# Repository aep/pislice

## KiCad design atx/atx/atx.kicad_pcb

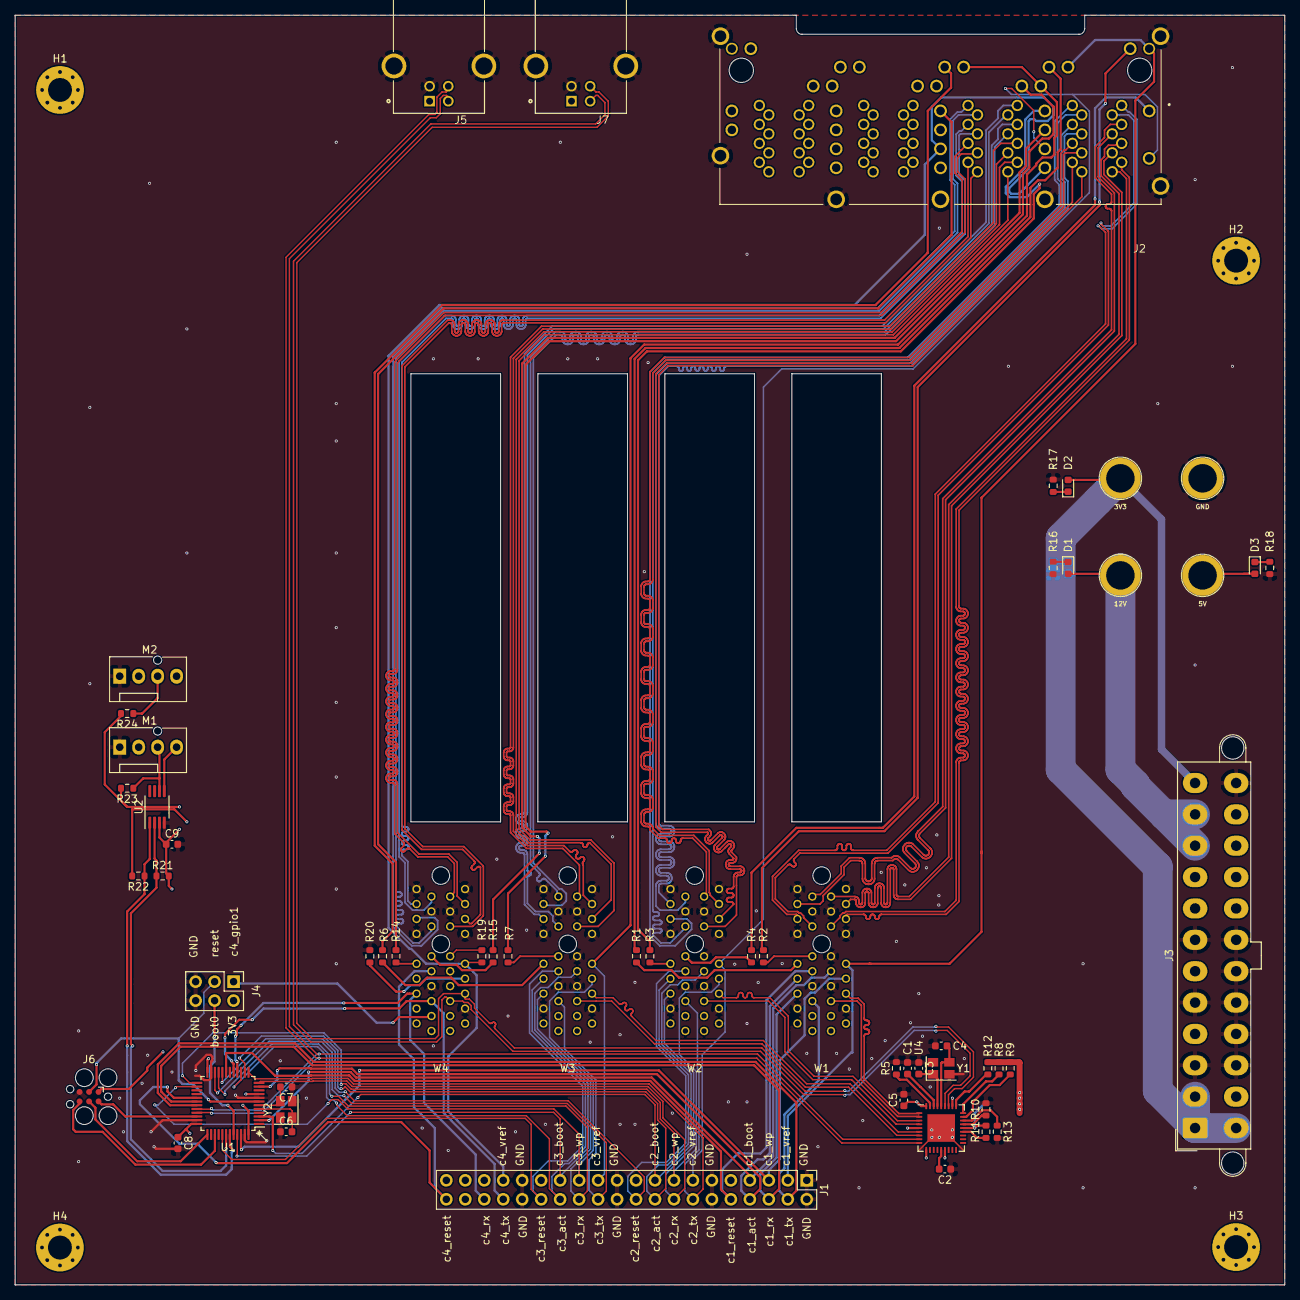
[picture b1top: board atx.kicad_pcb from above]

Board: 4 copper layers, 170.0 x 170.0 mm, 62 parts (0 on the bottom side), 116 nets.

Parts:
C1, C2: 0.1uF; C_0603_1608Metric
C3, C4, C6, C7: 14pF; C_0603_1608Metric
C5, C8: 10uF; C_0603_1608Metric
C9: 100nF; C_0603_1608Metric
D1, D2, D3: LED; LED_0603_1608Metric
H1, H2, H3, H4: MountingHole; MountingHole_3.2mm_M3_Pad_Via
J1: 2x20; PinHeader_2x20_P2.54mm_Vertical
J2: SS-74500-024; BEL_SS-74500-024
J3: ATX-24; Molex_Mini-Fit_Jr_5566-24A2_2x12_P4.20mm_Vertical
J4: Conn_02x03_Odd_Even; PinHeader_2x03_P2.54mm_Vertical
J5, J7: USB_B; CUI_UJ2-BH-1-TH
J6: Conn_02x03_Odd_Even; Tag-Connect_TC2030-IDC-FP_2x03_P1.27mm_Vertical
M1, M2: Fan_4pin; FanPinHeader_1x04_P2.54mm_Vertical
R1, R2, R3, R4, R6, R7, R14, R15, R17, R18: 300R; R_0603_1608Metric
R5: 12K 1%; R_0603_1608Metric
R8, R9, R10, R11, R12, R13: 10K; R_0603_1608Metric
R16, R19, R20: 1K; R_0603_1608Metric
R21, R22: 3K; R_0603_1608Metric
R23, R24: 36K 1%; R_0603_1608Metric
TP1: 12V; BANANA_CONN
TP2: 5V; BANANA_CONN
TP3: 3V3; BANANA_CONN
TP4: GND; BANANA_CONN
U1: STM32L151C8T6; LQFP-48_7x7mm_P0.5mm
U2: EMC2301; MSOP-8_3x3mm_P0.65mm
U4: USB2514B_Bi; QFN-36-1EP_6x6mm_P0.5mm_EP3.7x3.7mm
W1, W2, W3, W4: pislice-v1-PCIE-1X; piwing_pcie1
Y1, Y2: 24Mhz X1E0000210264; Crystal_SMD_SeikoEpson_TSX3225-4Pin_3.2x2.5mm

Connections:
+3V3: C5.1, C8.1, C9.1, D2.2, J3.1, J3.2, J3.12, J3.13, J4.2, J6.1, R8.2, R9.2, R11.2, R12.2, R21.2, R22.2, R23.2, R24.2, TP3.1, U1.9, U1.24, U1.36, U1.48, U2.3, U4.5, U4.10, U4.15, U4.23, U4.29, U4.36
+5V: D3.2, J3.4, J3.6, J3.21, J3.22, J3.23, TP2.1, W1.A1, W1.A2, W1.B1, W1.B2, W2.A1, W2.A2, W2.B1, W2.B2, W3.A1, W3.A2, W3.B1, W3.B2, W4.A1, W4.A2, W4.B1, W4.B2
+12V: D1.2, J3.10, J3.11, M1.2, M2.2, TP1.1
/c1_act: J1.8, U1.11, W1.A8
/c1_boot: J1.7, U1.2, W1.B9
/c1_eth_act: J2.12_1, R1.1
/c1_eth_link: J2.10_1, R2.1
/c1_eth_p1+: J2.8_1, W1.B13
/c1_eth_p1-: J2.7_1, W1.B14
/c1_eth_p2+: J2.6_1, W1.B16
/c1_eth_p2-: J2.5_1, W1.B17
/c1_eth_p3+: J2.4_1, W1.A16
/c1_eth_p3-: J2.3_1, W1.A17
/c1_eth_p4+: J2.2_1, W1.A13
/c1_eth_p4-: J2.1_1, W1.A14
/c1_reset: J1.10, U1.19, W1.A9
/c1_rx: J1.6, U1.30, W1.A6
/c1_tx: J1.4, U1.31, W1.A5
/c1_usb+: U4.2, W1.B5
/c1_usb-: U4.1, W1.B6
/c1_vref: J1.3, J2.9_1, J2.11_1, W1.B10
/c1_wp: J1.5, U1.46, W1.B8
/c2_act: J1.18, U1.14, W2.A8
/c2_boot: J1.17, U1.3, W2.B9
/c2_eth_act: J2.12_2, R3.1
/c2_eth_link: J2.10_2, R4.1
/c2_eth_p1+: J2.8_2, W2.B13
/c2_eth_p1-: J2.7_2, W2.B14
/c2_eth_p2+: J2.6_2, W2.B16
/c2_eth_p2-: J2.5_2, W2.B17
/c2_eth_p3+: J2.4_2, W2.A16
/c2_eth_p3-: J2.3_2, W2.A17
/c2_eth_p4+: J2.2_2, W2.A13
/c2_eth_p4-: J2.1_2, W2.A14
/c2_reset: J1.20, U1.20, W2.A9
/c2_rx: J1.16, U1.12, W2.A6
/c2_tx: J1.14, U1.13, W2.A5
/c2_usb+: U4.4, W2.B5
/c2_usb-: U4.3, W2.B6
/c2_vref: J1.13, J2.9_2, J2.11_2, W2.B10
/c2_wp: J1.15, U1.25, W2.B8
/c3_act: J1.28, U1.15, W3.A8
/c3_boot: J1.27, U1.45, W3.B9
/c3_eth_act: J2.12_3, R6.1
/c3_eth_link: J2.10_3, R7.1
/c3_eth_p1+: J2.8_3, W3.B13
/c3_eth_p1-: J2.7_3, W3.B14
/c3_eth_p2+: J2.6_3, W3.B16
/c3_eth_p2-: J2.5_3, W3.B17
/c3_eth_p3+: J2.4_3, W3.A16
/c3_eth_p3-: J2.3_3, W3.A17
/c3_eth_p4+: J2.2_3, W3.A13
/c3_eth_p4-: J2.1_3, W3.A14
/c3_reset: J1.30, U1.41, W3.A9
/c3_rx: J1.26, U1.21, W3.A6
/c3_tx: J1.24, U1.22, W3.A5
/c3_usb+: U4.7, W3.B5
/c3_usb-: U4.6, W3.B6
/c3_vref: J1.23, J2.9_3, J2.11_3, W3.B10
/c3_wp: J1.25, U1.26, W3.B8
/c4_eth_act: J2.12_4, R14.1
/c4_eth_link: J2.10_4, R15.1
/c4_eth_p1+: J2.8_4, W4.B13
/c4_eth_p1-: J2.7_4, W4.B14
/c4_eth_p2+: J2.6_4, W4.B16
/c4_eth_p2-: J2.5_4, W4.B17
/c4_eth_p3+: J2.4_4, W4.A16
/c4_eth_p3-: J2.3_4, W4.A17
/c4_eth_p4+: J2.2_4, W4.A13
/c4_eth_p4-: J2.1_4, W4.A14
/c4_gpio1: J4.1, W4.A3
/c4_reset: J1.40, U1.29, W4.A9
/c4_rx: J1.36, U1.16, W4.A6
/c4_tx: J1.34, U1.17, W4.A5
/c4_vref: J1.33, J2.9_4, J2.11_4, R19.2, W4.B10
/mcu_reset: J4.3, J6.3, U1.7
/mcu_scl: R21.1, U1.42, U2.2
/mcu_sda: R22.1, U1.43, U2.1
/mcu_swclk: J6.4, U1.37
/mcu_swdio: J6.2, U1.34
/mcu_tdo: J6.6, U1.39
/mcu_usb+: J5.3, U1.33, U4.9
/mcu_usb-: J5.2, U1.32, U4.8
/root_usb+: J7.2, U4.31, W4.B5
/root_usb-: J7.3, U4.30, W4.B6
GND: C1.1, C2.1, C3.1, C4.1, C5.2, C6.1, C7.1, C8.2, C9.2, J1.1, J1.2, J1.11, J1.12, J1.21, J1.22, J1.31, J1.32, J2.S1, J2.S2, J2.S3, J2.S4, J2.S5, J2.S6, J2.S7, J3.3, J3.5, J3.7, J3.15, J3.16, J3.17, J3.18, J3.19, J3.24, J4.5, J4.6, J5.4, J5.5, J6.5, J7.4, J7.5, M1.1, M2.1, R5.2, R10.2, R13.2, R16.2, R17.2, R18.2, R20.2, TP4.1, U1.8, U1.23, U1.35, U1.47, U2.4, U4.37, W1.A4, W1.A7, W1.A12, W1.A15, W1.A18, W1.B4, W1.B7, W1.B11, W1.B12, W1.B15, W1.B18, W2.A4, W2.A7, W2.A12, W2.A15, W2.A18, W2.B4, W2.B7, W2.B11, W2.B12, W2.B15, W2.B18, W3.A4, W3.A7, W3.A12, W3.A15, W3.A18, W3.B4, W3.B7, W3.B11, W3.B12, W3.B15, W3.B18, W4.A4, W4.A7, W4.A12, W4.A15, W4.A18, W4.B4, W4.B7, W4.B12, W4.B15, W4.B18, Y1.2, Y1.4, Y2.2, Y2.4
unnamed: C1.2, U4.34
unnamed: C2.2, U4.14
unnamed: C3.2, U4.33, Y1.1
unnamed: C4.2, U4.32, Y1.3
unnamed: C6.2, U1.5, Y2.1
unnamed: C7.2, U1.6, Y2.3
unnamed: D1.1, R16.1
unnamed: D2.1, R17.1
unnamed: D3.1, R18.1
unnamed: J4.4, U1.44
unnamed: M1.3, R23.1, U2.6
unnamed: M1.4, U2.5
unnamed: M2.3, R24.1
unnamed: R1.2, W1.A10
unnamed: R2.2, W1.A11
unnamed: R3.2, W2.A10
unnamed: R4.2, W2.A11
unnamed: R5.1, U4.35
unnamed: R6.2, W3.A10
unnamed: R7.2, W3.A11
unnamed: R8.1, U4.27
unnamed: R9.1, U4.26
unnamed: R10.1, U4.24
unnamed: R11.1, U4.22
unnamed: R12.1, U4.28
unnamed: R13.1, U4.25
unnamed: R14.2, W4.A10
unnamed: R15.2, W4.A11
unnamed: R19.1, W4.B11
unnamed: R20.1, W4.B8

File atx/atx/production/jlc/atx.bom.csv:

Comment,Designator,Footprint,LCSC Part #
0.1uF,C1,C_0603_1608Metric,
0.1uF,C2,C_0603_1608Metric,
14pF,C3,C_0603_1608Metric,
14pF,C4,C_0603_1608Metric,
10uF,C5,C_0603_1608Metric,
14pF,C6,C_0603_1608Metric,
14pF,C7,C_0603_1608Metric,
10uF,C8,C_0603_1608Metric,
100nF,C9,C_0603_1608Metric,
LED,D1,LED_0603_1608Metric,
LED,D2,LED_0603_1608Metric,
LED,D3,LED_0603_1608Metric,
2x20,J1,PinHeader_2x20_P2.54mm_Vertical,
SS-74500-024,J2,BEL_SS-74500-024,
ATX-24,J3,Molex_Mini-Fit_Jr_5566-24A2_2x12_P4.20mm_Vertical,
Conn_02x03_Odd_Even,J4,PinHeader_2x03_P2.54mm_Vertical,
USB_B,J5,CUI_UJ2-BH-1-TH,
USB_B,J7,CUI_UJ2-BH-1-TH,
Fan_4pin,M1,FanPinHeader_1x04_P2.54mm_Vertical,
Fan_4pin,M2,FanPinHeader_1x04_P2.54mm_Vertical,
300R,R1,R_0603_1608Metric,
10K,R10,R_0603_1608Metric,
10K,R11,R_0603_1608Metric,
10K,R12,R_0603_1608Metric,
10K,R13,R_0603_1608Metric,
300R,R14,R_0603_1608Metric,
300R,R15,R_0603_1608Metric,
1K,R16,R_0603_1608Metric,
300R,R17,R_0603_1608Metric,
300R,R18,R_0603_1608Metric,
1K,R19,R_0603_1608Metric,
300R,R2,R_0603_1608Metric,
1K,R20,R_0603_1608Metric,
3K,R21,R_0603_1608Metric,
3K,R22,R_0603_1608Metric,
36K 1%,R23,R_0603_1608Metric,
36K 1%,R24,R_0603_1608Metric,
300R,R3,R_0603_1608Metric,
300R,R4,R_0603_1608Metric,
12K 1%,R5,R_0603_1608Metric,
300R,R6,R_0603_1608Metric,
300R,R7,R_0603_1608Metric,
10K,R8,R_0603_1608Metric,
10K,R9,R_0603_1608Metric,
STM32L151C8T6,U1,LQFP-48_7x7mm_P0.5mm,
EMC2301,U2,MSOP-8_3x3mm_P0.65mm,
USB2514B_Bi,U4,QFN-36-1EP_6x6mm_P0.5mm_EP3.7x3.7mm,
pislice-v1-PCIE-1X,W1,piwing_pcie1,
pislice-v1-PCIE-1X,W2,piwing_pcie1,
pislice-v1-PCIE-1X,W3,piwing_pcie1,
pislice-v1-PCIE-1X,W4,piwing_pcie1,
24Mhz X1E0000210264,Y1,Crystal_SMD_SeikoEpson_TSX3225-4Pin_3.2x2.5mm,
24Mhz X1E0000210264,Y2,Crystal_SMD_SeikoEpson_TSX3225-4Pin_3.2x2.5mm,

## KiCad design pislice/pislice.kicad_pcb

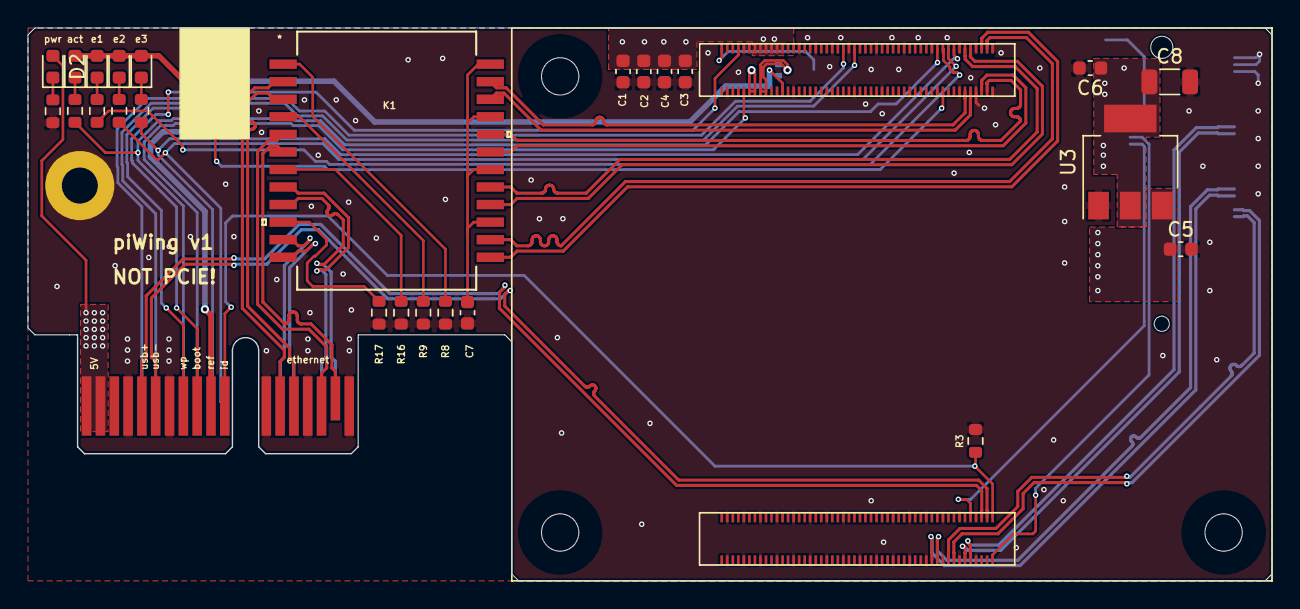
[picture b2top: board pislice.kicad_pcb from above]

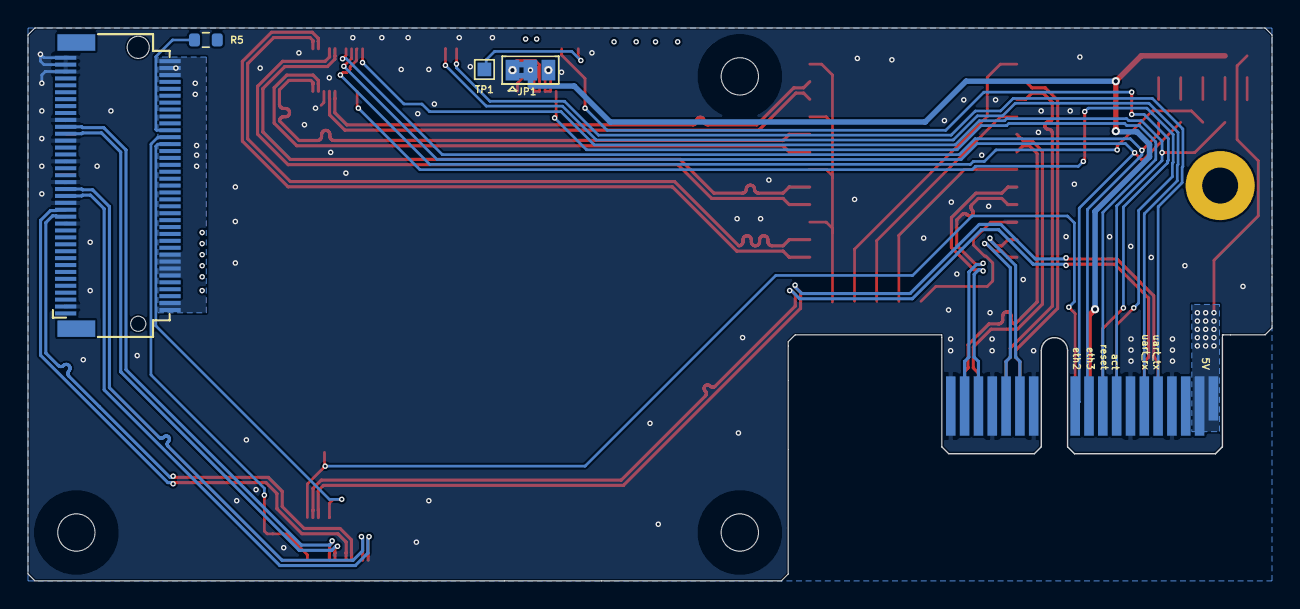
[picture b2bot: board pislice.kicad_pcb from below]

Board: 4 copper layers, 90.0 x 40.0 mm, 31 parts (4 on the bottom side), 54 nets.

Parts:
C1, C2, C4: 10uf; C_0603_1608Metric
C3: 100pF; C_0603_1608Metric
C5, C6: 10uF; C_0603_1608Metric
C7: 100nF; C_0603_1608Metric
C8: 10uF; C_1206_3216Metric
D1, D2, D3, D4, D5: LED; LED_0603_1608Metric
JP1: SolderJumper_3_Bridged12; SolderJumper-3_P1.3mm_Bridged2Bar12_Pad1.0x1.5mm
K1: HX6096NL
R1, R2, R3, R4, R11: 300R; R_0603_1608Metric
R5: DNC; R_0603_1608Metric
R6: 600R; R_0603_1608Metric
R8, R9, R16, R17: 75R; R_0603_1608Metric
TP1: TestPoint; TestPoint_Pad_1.0x1.0mm
U1: Conn_TE-M.2-0.5-67P; Conn_TE-M.2-0.5-67P-NVME
U2: RPI4CM-aep; rpiCM4
U3: AZ1117CH-3_3TRG1; SOT-223
U14: PCIE-1X; BUS_PCIexpress_x1

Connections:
+3V3: C6.1, C8.1, U1.2, U1.4, U1.12, U1.14, U1.16, U1.18, U1.70, U1.72, U1.74, U3.2, U3.4
+5V: C1.1, C2.1, C3.1, C4.1, C5.1, D3.2, U2.77, U2.79, U2.81, U2.83, U2.85, U2.87, U3.3, U14.A1, U14.A2, U14.B1, U14.B2
GND: C1.2, C2.2, C3.2, C4.2, C5.2, C6.2, C7.2, C8.2, R3.1, R6.1, R8.2, R9.2, R16.2, R17.2, U1.3, U1.27, U1.33, U1.39, U1.45, U1.51, U1.57, U1.71, U1.73, U1.75, U2.1, U2.2, U2.7, U2.8, U2.13, U2.14, U2.22, U2.23, U2.32, U2.33, U2.42, U2.43, U2.52, U2.53, U2.59, U2.60, U2.65, U2.71, U2.74, U2.89, U2.91, U2.98, U2.107, U2.108, U2.113, U2.114, U2.119, U2.120, U2.125, U2.126, U2.131, U2.132, U2.137, U2.138, U2.144, U2.150, U2.155, U2.156, U2.161, U2.162, U2.167, U2.168, U2.173, U2.174, U2.179, U2.180, U2.185, U2.186, U2.191, U2.192, U2.197, U2.198, U3.1, U14.A4, U14.A7, U14.A12, U14.A15, U14.A18, U14.B4, U14.B7, U14.B12, U14.B15, U14.B18
GPIO_REF: D1.2, D2.2, D4.2, D5.2, JP1.2, U2.78, U14.B10
unnamed: C7.1, K1.15, K1.18, K1.21, K1.24
unnamed: D1.1, R11.2
unnamed: D2.1, R4.2
unnamed: D3.1, R6.2
unnamed: D4.1, R1.2
unnamed: D5.1, R2.2
unnamed: JP1.1, U2.84, U2.86
unnamed: JP1.3, U2.88, U2.90
unnamed: K1.1, R8.1
unnamed: K1.4, R9.1
unnamed: K1.7, R16.1
unnamed: K1.10, R17.1
unnamed: R4.1, U2.19
unnamed: R5.1, U1.54
unnamed: TP1.1, U2.99
c1-eeprom_wp: U2.20, U14.B8
c1-eth-led2: R11.1, U2.17, U14.A11
c1-eth-led3: R1.1, U2.15, U14.A10
c1-eth-p1+: K1.23, U2.12
c1-eth-p1-: K1.22, U2.10
c1-eth-p2+: K1.20, U2.4
c1-eth-p2-: K1.19, U2.6
c1-eth-p3+: K1.17, U2.11
c1-eth-p3-: K1.16, U2.9
c1-eth-p4+: K1.14, U2.3
c1-eth-p4-: K1.13, U2.5
c1-led-activity: R2.1, U2.21, U14.A8
c1-pcie-clk+: U1.55, U2.110
c1-pcie-clk-: U1.53, U2.112
c1-pcie-clk-nreq: U1.52, U2.102
c1-pcie-nrst: U1.50, U2.109
c1-pcie-rx+: U1.31, U2.116
c1-pcie-rx-: U1.29, U2.118
c1-pcie-tx+: U1.37, U2.122
c1-pcie-tx-: U1.35, U2.124
c1-rpiboot: U2.93, U14.B9
c1-run-reset: U2.92, U14.A9
c1-usb-d+: U2.105, U14.B5
c1-usb-d-: U2.103, U14.B6
c1-usb-otg-id: R3.2, U2.101, U14.B11
c1_UART_RX: U2.51, U14.A6
c1_UART_TX: U2.55, U14.A5
eth-p1+: K1.2, U14.B13
eth-p1-: K1.3, U14.B14
eth-p2+: K1.5, U14.B16
eth-p2-: K1.6, U14.B17
eth-p3+: K1.8, U14.A16
eth-p3-: K1.9, U14.A17
eth-p4+: K1.11, U14.A13
eth-p4-: K1.12, U14.A14

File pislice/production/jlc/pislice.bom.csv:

Comment,Designator,Footprint,LCSC Part #
10uf,C1,C_0603_1608Metric,
10uf,C2,C_0603_1608Metric,
100pF,C3,C_0603_1608Metric,
10uf,C4,C_0603_1608Metric,
10uF,C5,C_0603_1608Metric,
10uF,C6,C_0603_1608Metric,
100nF,C7,C_0603_1608Metric,
10uF,C8,C_1206_3216Metric,
LED,D1,LED_0603_1608Metric,
LED,D2,LED_0603_1608Metric,
LED,D3,LED_0603_1608Metric,
LED,D4,LED_0603_1608Metric,
LED,D5,LED_0603_1608Metric,
HX6096NL,K1,HX6096NL,
300R,R1,R_0603_1608Metric,
300R,R11,R_0603_1608Metric,
75R,R16,R_0603_1608Metric,
75R,R17,R_0603_1608Metric,
300R,R2,R_0603_1608Metric,
300R,R3,R_0603_1608Metric,
300R,R4,R_0603_1608Metric,
DNC,R5,R_0603_1608Metric,
600R,R6,R_0603_1608Metric,
75R,R8,R_0603_1608Metric,
75R,R9,R_0603_1608Metric,
Conn_TE-M.2-0.5-67P,U1,Conn_TE-M.2-0.5-67P-NVME,
RPI4CM-aep,U2,rpiCM4,
AZ1117CH-3_3TRG1,U3,SOT-223,
dummy,X2,HRS_DF40HC(3.0)-100DS-0.4V(58,
dummy,X3,HRS_DF40HC(3.0)-100DS-0.4V(58,

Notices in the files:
parts and their libraries:
Copyright 2016 Accelerated Designs. All rights reserved.
